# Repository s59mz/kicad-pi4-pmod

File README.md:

# pi4_pmod
Raspbery Pi-4 Adapter for Pmod modules

Schematic:
[pi4_pmod.pdf](pi4_pmod.pdf)

BOM:
[pi4_pmod.csv](pi4_pmod.csv)

Gerbers:
[gerbers.zip](https://github.com/s59mz/kicad-pi4-pmod/raw/main/gerbers.zip)

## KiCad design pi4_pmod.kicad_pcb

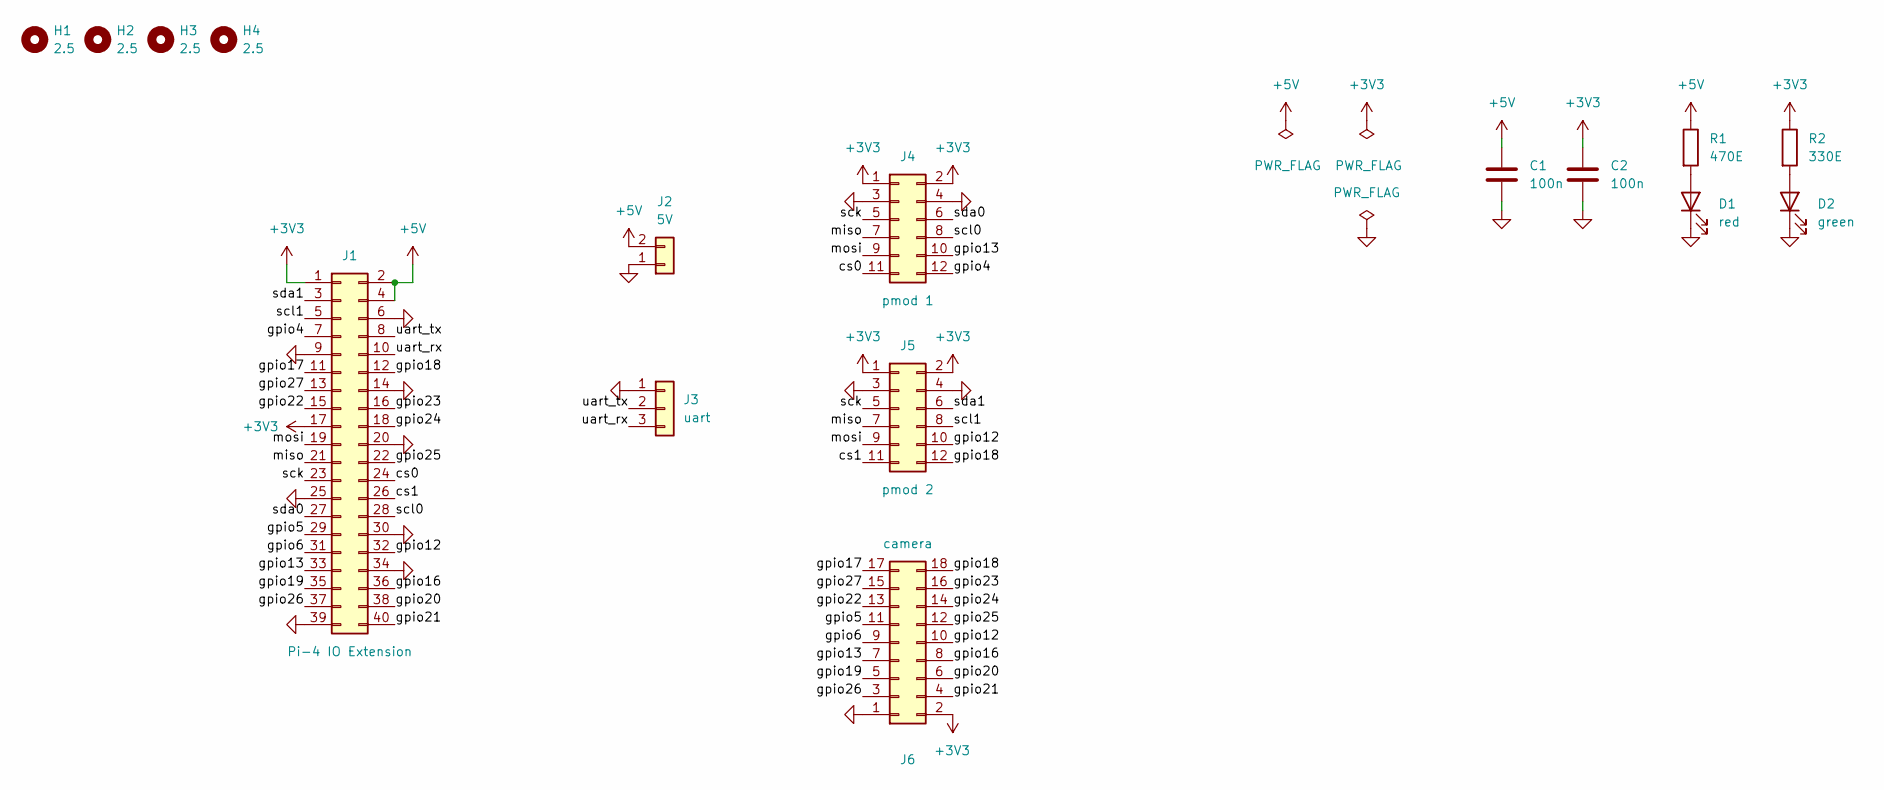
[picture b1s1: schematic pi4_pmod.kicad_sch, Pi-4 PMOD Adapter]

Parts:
C1, C2: 100n; C_0603_1608Metric_Pad1.08x0.95mm_HandSolder
D1: red; LED_0603_1608Metric_Pad1.05x0.95mm_HandSolder
D2: green; LED_0603_1608Metric_Pad1.05x0.95mm_HandSolder
H1, H2, H3, H4: 2.5; MountingHole_2.5mm
J1: Pi-4 IO Extension; PinHeader_2x20_P2.54mm_Vertical
J2: 5V; PinHeader_1x02_P2.54mm_Vertical
J3: uart; PinHeader_1x03_P2.54mm_Vertical
J4: pmod 1; PinSocket_2x06_P2.54mm_Horizontal
J5: pmod 2; PinSocket_2x06_P2.54mm_Horizontal
J6: camera; PinSocket_2x09_P2.54mm_Horizontal
R1: 470E; R_0603_1608Metric_Pad0.98x0.95mm_HandSolder
R2: 330E; R_0603_1608Metric_Pad0.98x0.95mm_HandSolder

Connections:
+3V3: C2.1, J1.1, J1.17, J4.1, J4.2, J5.1, J5.2, J6.2, R2.1
+5V: C1.1, J1.2, J1.4, J2.2, R1.1
/cs0: J1.24, J4.11
/cs1: J1.26, J5.11
/gpio4: J1.7, J4.12
/gpio5: J1.29, J6.11
/gpio6: J1.31, J6.9
/gpio12: J1.32, J5.10, J6.10
/gpio13: J1.33, J4.10, J6.7
/gpio16: J1.36, J6.8
/gpio17: J1.11, J6.17
/gpio18: J1.12, J5.12, J6.18
/gpio19: J1.35, J6.5
/gpio20: J1.38, J6.6
/gpio21: J1.40, J6.4
/gpio22: J1.15, J6.13
/gpio23: J1.16, J6.16
/gpio24: J1.18, J6.14
/gpio25: J1.22, J6.12
/gpio26: J1.37, J6.3
/gpio27: J1.13, J6.15
/miso: J1.21, J4.7, J5.7
/mosi: J1.19, J4.9, J5.9
/sck: J1.23, J4.5, J5.5
/scl0: J1.28, J4.8
/scl1: J1.5, J5.8
/sda0: J1.27, J4.6
/sda1: J1.3, J5.6
/uart_rx: J1.10, J3.3
/uart_tx: J1.8, J3.2
GND: C1.2, C2.2, D1.1 (K), D2.1 (K), J1.6, J1.9, J1.14, J1.20, J1.25, J1.30, J1.34, J1.39, J2.1, J3.1, J4.3, J4.4, J5.3, J5.4, J6.1
unnamed: D1.2 (A), R1.2
unnamed: D2.2 (A), R2.2

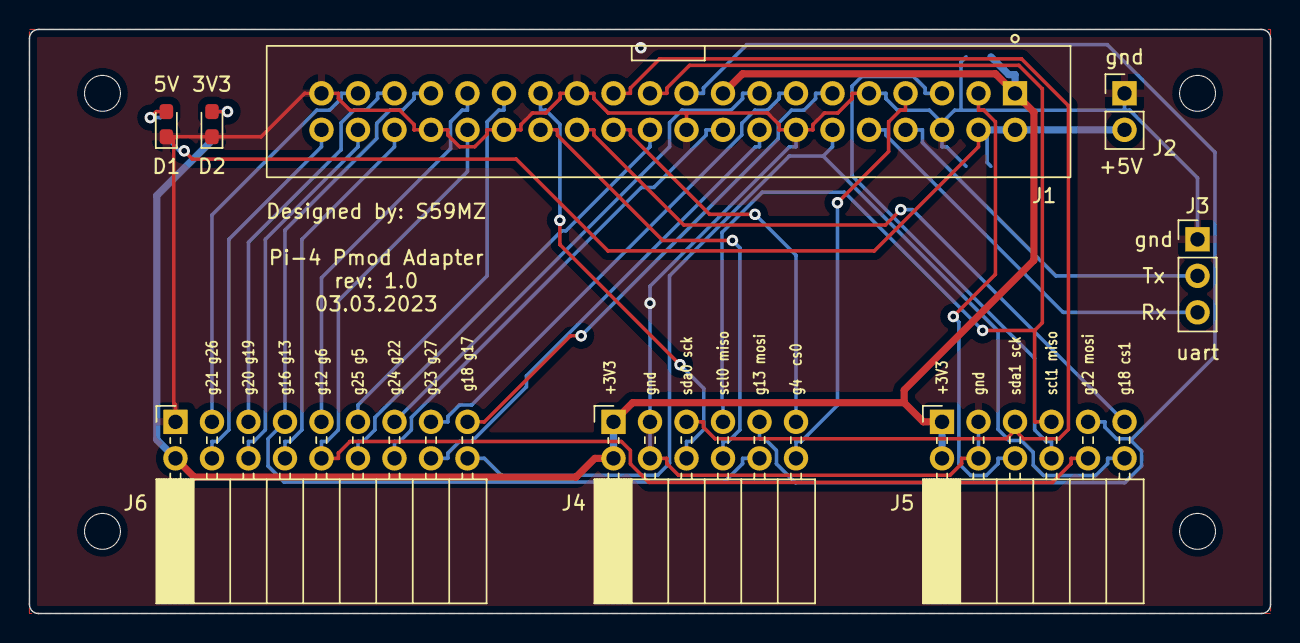
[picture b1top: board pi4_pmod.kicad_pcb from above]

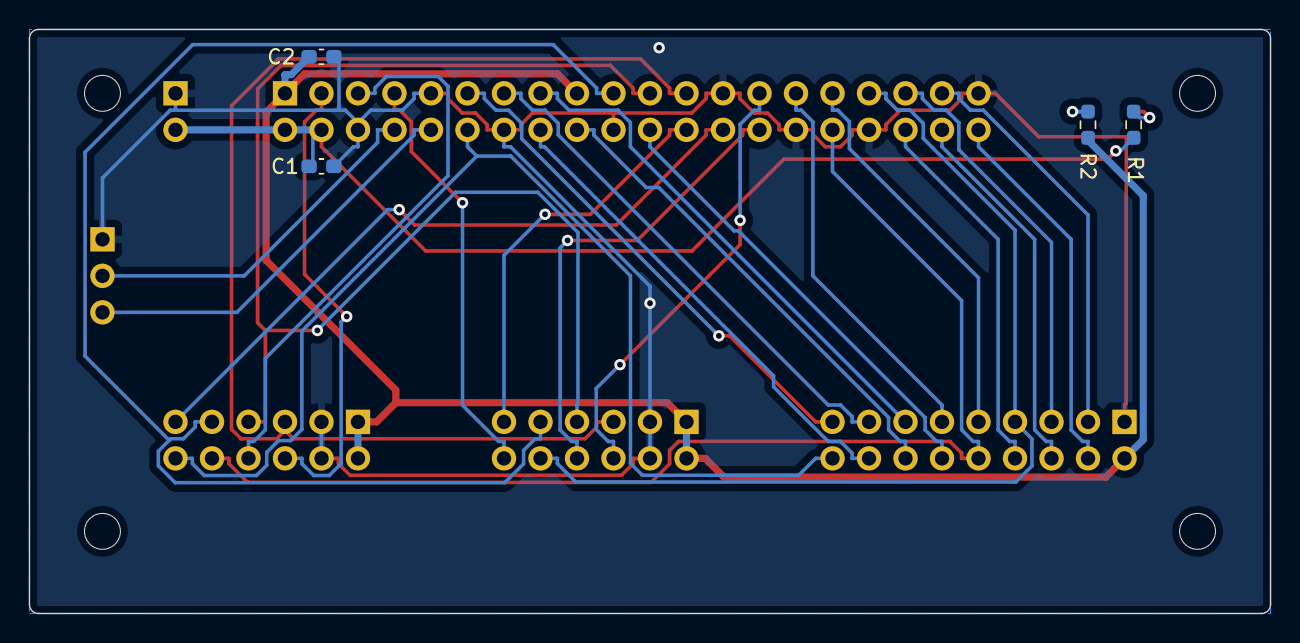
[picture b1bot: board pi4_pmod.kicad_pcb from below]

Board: 2 copper layers, 86.4 x 40.6 mm, 16 parts (4 on the bottom side), 33 nets.

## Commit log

2024-08-11 add screenshots
